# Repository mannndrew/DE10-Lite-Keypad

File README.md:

# DE10-Lite Keypad

A modern design on a PCB keypad with KiCad to be used on the DE10-Lite FPGA or with other similar device pin headers including the Arduino UNO R3.

---

## Repository Structure
The repository is organized as follows:

- `Documentation/`: Holds images and visual assets related to the project.
- `Keypad/`: Includes KiCad project files.
- `PCBWay/`: Contains assembly instructions and pricing documentation.

---

## Schematic

---

## PCB

---

## 3D Model

---

## License
This is published under the [MIT License](https://opensource.org/licenses/MIT).

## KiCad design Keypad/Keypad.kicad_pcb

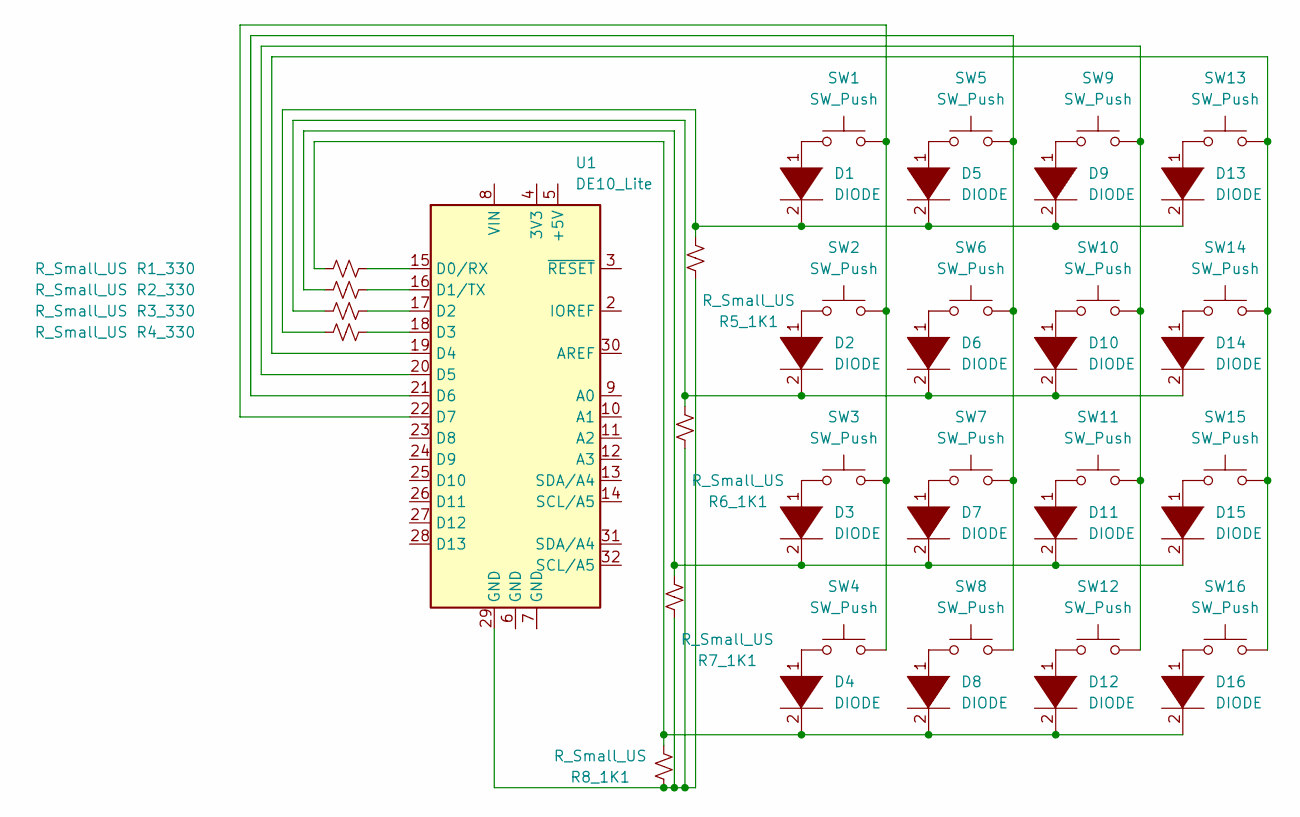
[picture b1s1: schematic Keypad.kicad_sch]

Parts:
D1, D2, D3, D4, D5, D6, D7, D8, D9, D10, D11, D12, D13, D14, D15, D16: DIODE; D_SOD-123
R1_330, R2_330, R3_330, R4_330, R5_1K1, R6_1K1, R7_1K1, R8_1K1: R_Small_US; R_0603_1608Metric
SW1, SW2, SW3, SW4, SW5, SW6, SW7, SW8, SW9, SW10, SW11, SW12, SW13, SW14, SW15, SW16: SW_Push; SW_SPST_TL3305B
U1: DE10_Lite

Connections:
unnamed: D1.1 (K), SW1.1
unnamed: D1.2 (A), D5.2 (A), D9.2 (A), D13.2 (A), R4_330.2, R5_1K1.2
unnamed: D2.1 (K), SW2.1
unnamed: D3.1 (K), SW3.1
unnamed: D4.1 (K), SW4.1
unnamed: D5.1 (K), SW5.1
unnamed: D6.1 (K), SW6.1
unnamed: D7.1 (K), SW7.1
unnamed: D8.1 (K), SW8.1
unnamed: D9.1 (K), SW9.1
unnamed: D10.1 (K), SW10.1
unnamed: D2.2 (A), D6.2 (A), D10.2 (A), D14.2 (A), R3_330.2, R6_1K1.2
unnamed: D11.1 (K), SW11.1
unnamed: D3.2 (A), D7.2 (A), D11.2 (A), D15.2 (A), R2_330.2, R7_1K1.2
unnamed: D12.1 (K), SW12.1
unnamed: D4.2 (A), D8.2 (A), D12.2 (A), D16.2 (A), R1_330.2, R8_1K1.2
unnamed: D13.1 (K), SW13.1
unnamed: D14.1 (K), SW14.1
unnamed: D15.1 (K), SW15.1
unnamed: D16.1 (K), SW16.1
unnamed: R1_330.1, U1.15 (D0/RX)
unnamed: R2_330.1, U1.16 (D1/TX)
unnamed: R3_330.1, U1.17 (D2)
unnamed: R4_330.1, U1.18 (D3)
unnamed: R5_1K1.1, R6_1K1.1, R7_1K1.1, R8_1K1.1, U1.29 (GND)
unnamed: SW1.2, SW2.2, SW3.2, SW4.2, U1.22 (D7)
unnamed: SW5.2, SW6.2, SW7.2, SW8.2, U1.21 (D6)
unnamed: SW9.2, SW10.2, SW11.2, SW12.2, U1.20 (D5)
unnamed: SW13.2, SW14.2, SW15.2, SW16.2, U1.19 (D4)

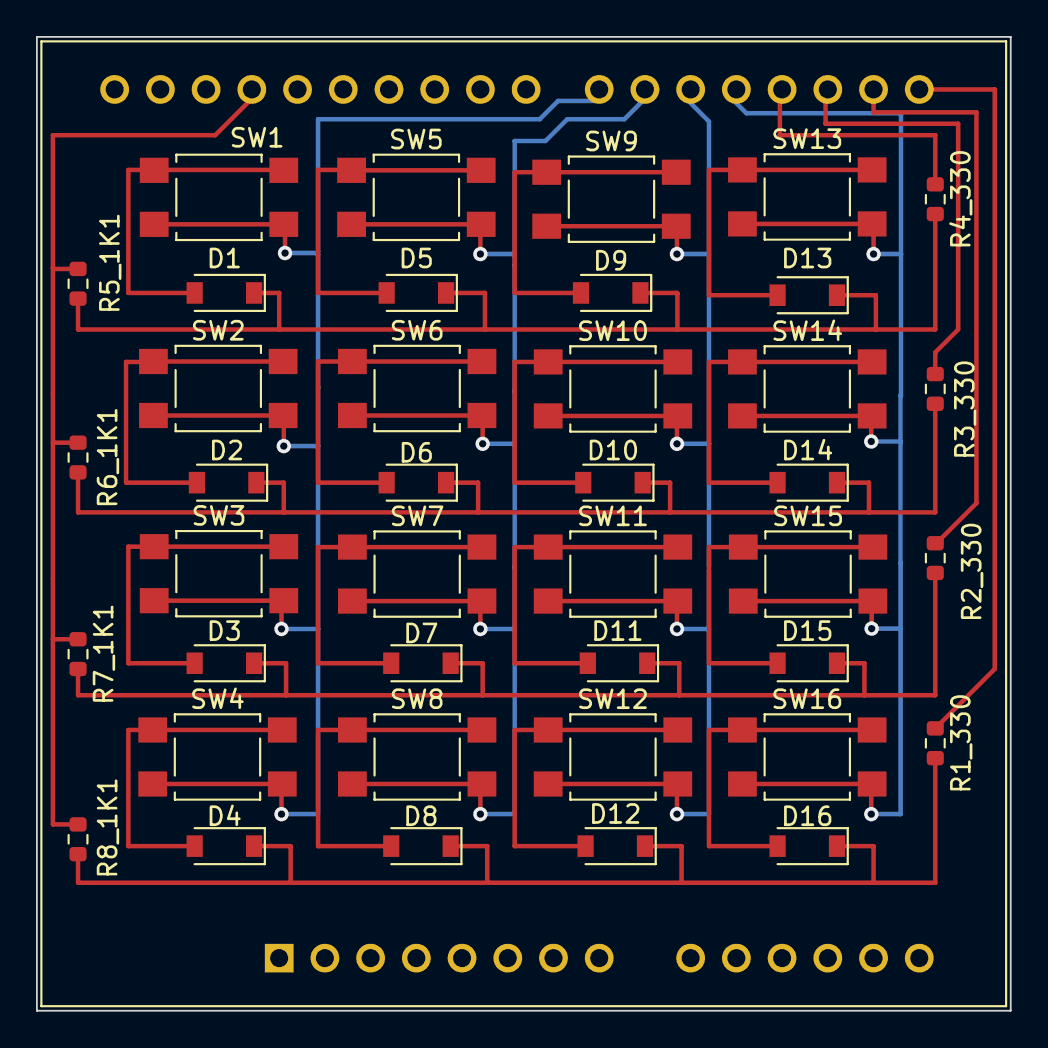
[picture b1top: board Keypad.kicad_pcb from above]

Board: 2 copper layers, 54.1 x 54.1 mm, 41 parts (0 on the bottom side), 29 nets.

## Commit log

2023-02-15 Added files
2023-08-09 Working on de10lite keypad 2.0
2023-08-10 Added in assembly and product files for PCBWay
2023-08-10 Removed unwanted files
2023-08-10 Added the quote for BOM
2023-08-10 Reorganized
2023-08-10 Added documentation
